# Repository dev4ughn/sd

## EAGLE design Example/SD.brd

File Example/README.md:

# SR Latch & Decade Counter Game

## Overview

Using an SR latch as the clock input for a decade counter to light up LEDs. The goal is to light up all the LEDs in the fastest time possible.

## Power Input

Two 3.0V coin cell lithium-ion batteries.

## SR Latch

Using two NOR gates on an IC. An LED will confirm the state of the SR latch.

## Decade Counter

Edge-triggered component that outputs high for a new pin every clock cycle.

## Firmware

This board does not have any programmable components so no firmware is required.

## Images

Schematic:

Board:

3D Render:

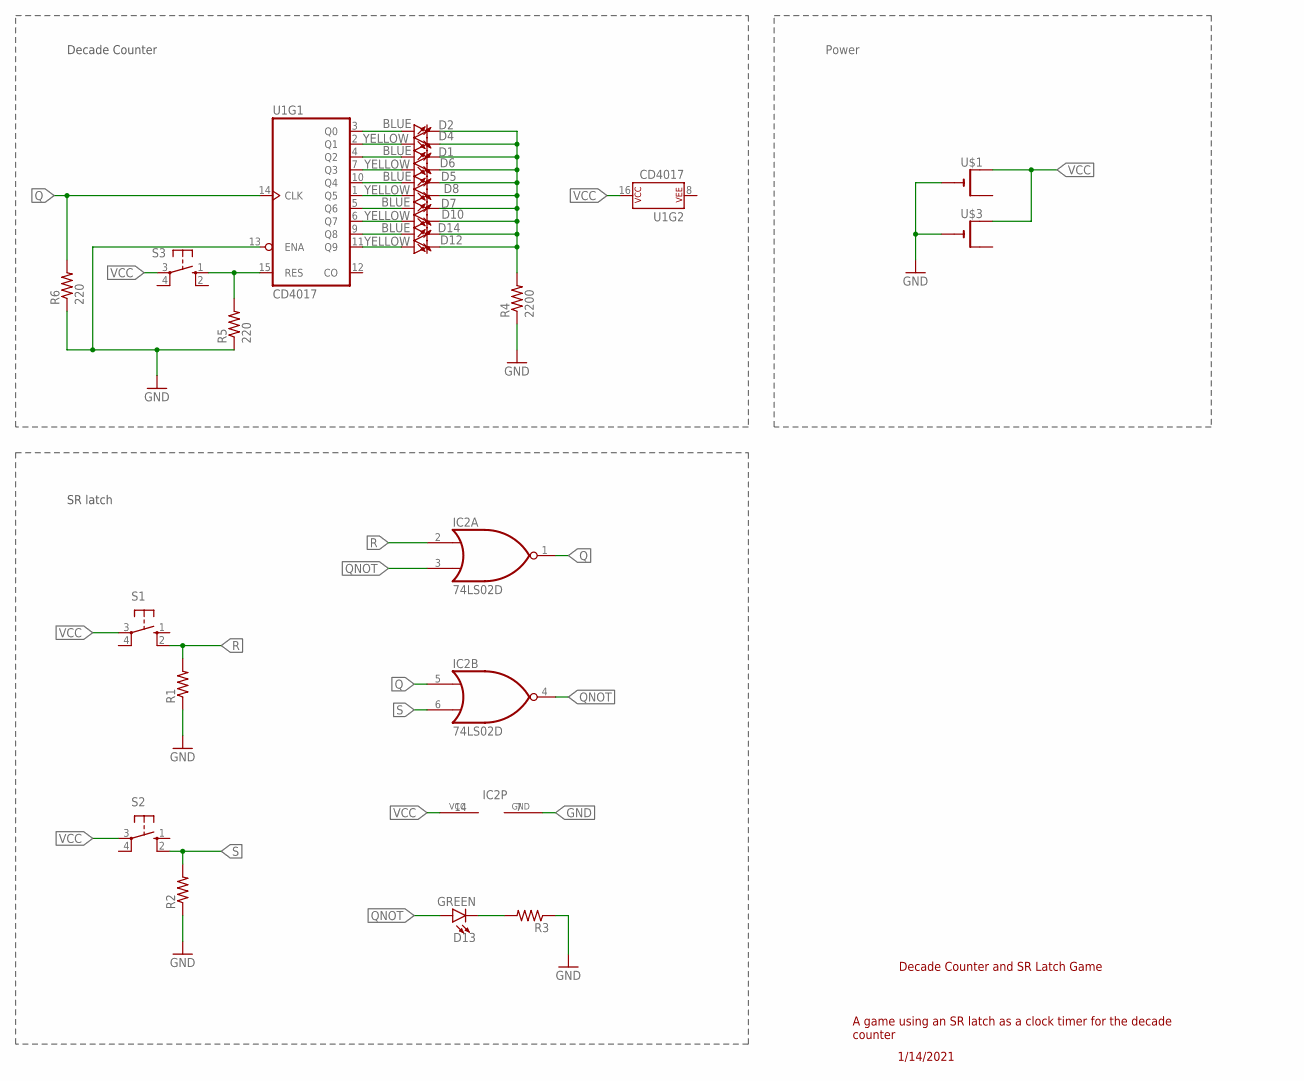
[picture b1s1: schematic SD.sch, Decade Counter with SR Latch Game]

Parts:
D1, D2, D5, D7, D14: BLUE; LED-0603
D4, D6, D8, D10, D12: YELLOW; LED0603
D13: GREEN; LED-0603
IC2: 74LS02D; SO14
R1, R2, R3: R-US_R0603; R0603
R4: 2200; R0603
R5, R6: 220; R0603
S1, S2, S3: 40-XX-ROUND; B3F-40XX-ROUND
U1: CD4017; DIP16
U$1, U$3: CR1220SMT; CR1220-SMD

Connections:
GND: IC2.7 (GND), R1.1, R2.1, R3.1, R4.1, R5.1, R6.1, U1.13 (ENA), U$1.-, U$3.-
unnamed: R5.2, S3.1 (S), U1.15 (RES)
unnamed: D13.C, R3.2
unnamed: D2.A, U1.3 (Q0)
unnamed: D4.A, U1.2 (Q1)
unnamed: D1.A, U1.4 (Q2)
unnamed: D6.A, U1.7 (Q3)
unnamed: D5.A, U1.10 (Q4)
unnamed: D8.A, U1.1 (Q5)
unnamed: D7.A, U1.5 (Q6)
unnamed: D10.A, U1.6 (Q7)
unnamed: D14.A, U1.9 (Q8)
unnamed: D12.A, U1.11 (Q9)
unnamed: D1.C, D2.C, D4.C, D5.C, D6.C, D7.C, D8.C, D10.C, D12.C, D14.C, R4.2
Q: IC2.1 (O), IC2.5 (I0), R6.2, U1.14 (CLK)
QNOT: IC2.3 (I1), IC2.4 (O)
R: IC2.2 (I0), R1.2, S1.2 (S1)
S: IC2.6 (I1), R2.2, S2.2 (S1)
VCC: IC2.14 (VCC), S1.3, S2.3, U1.16 (P$V+), U$1.+$1 (+), U$3.+$1 (+)

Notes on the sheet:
SR latch
Decade Counter
Power
Decade Counter and SR Latch Game
A game using an SR latch as a clock timer for the decade counter
1/14/2021

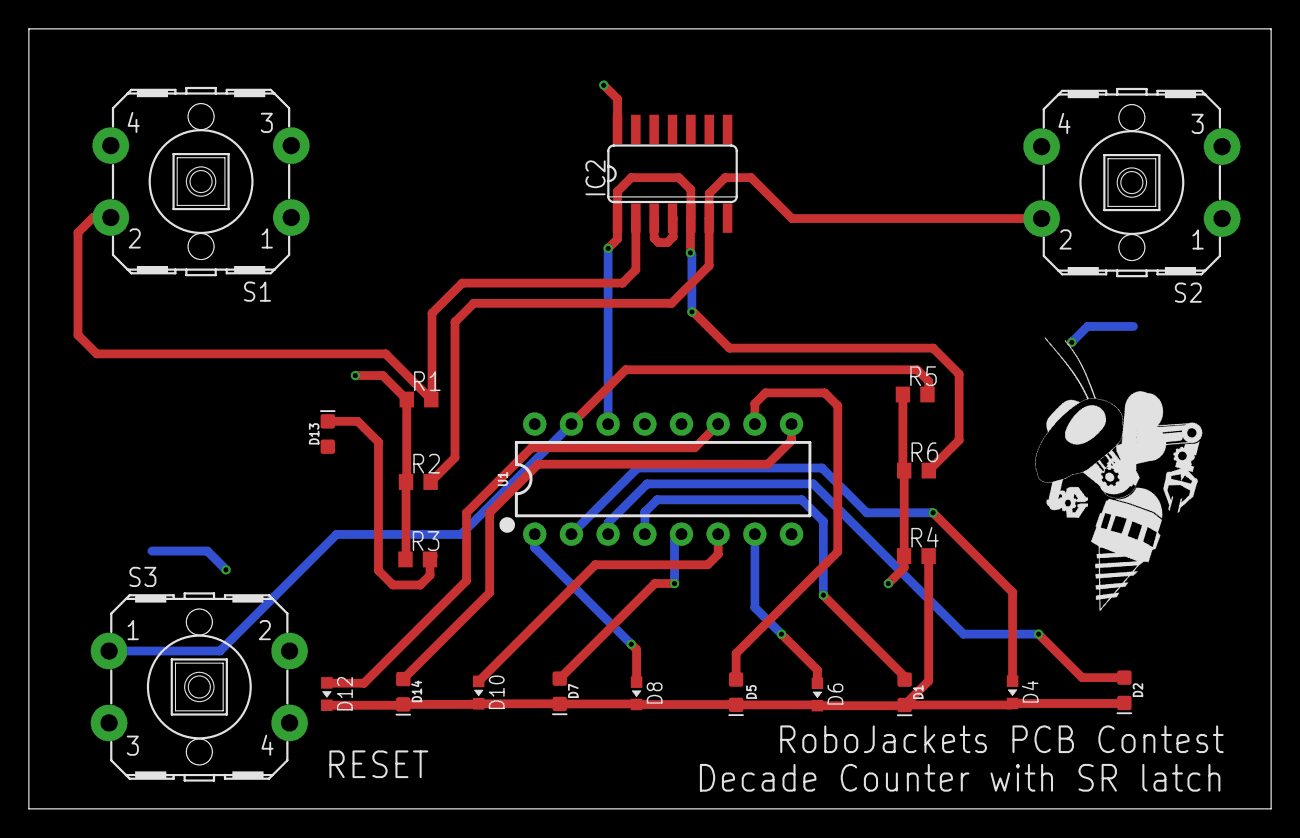
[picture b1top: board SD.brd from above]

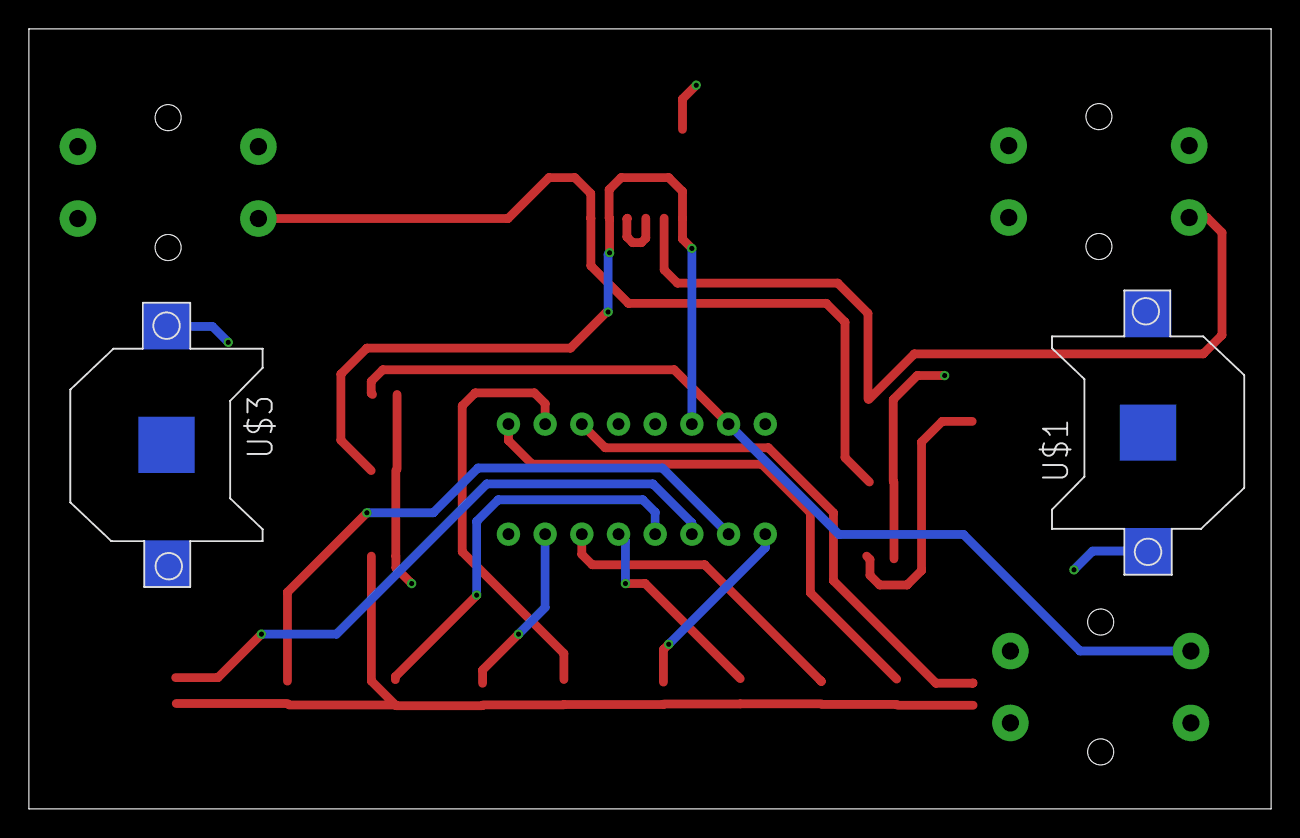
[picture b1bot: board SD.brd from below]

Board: 2 copper layers, 86.0 x 54.0 mm, 25 parts (2 on the bottom side), 19 nets.

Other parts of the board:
U$4: ROBOBUZZ_1.0X

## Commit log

2020-12-19 Delete motor
    commit test
2021-01-04 Update Example.sch
    Added labels to the schematic view of parts we need.
2021-01-08 added four new parts
    added button, cell, led, and nor gate
2021-01-09 add
    add parts
2021-01-09 Revert "add"
    This reverts commit c6e4ebc28e4f55c76fdda87922b953a09ff3b68b.
2021-01-09 sr latch
    finished sr latch
2021-01-10 Fixed issue of second NOR gate. However, did not delete second NOR gate.
    I could not change the attributes of the NOR gates.
2021-01-10 Added CD4017 Decade Counter
    Part can be found in the SparkFun-IC-Logiv Library
2021-01-12 decade counter
    leds for decade counter
2021-01-12 decade counter
    added clocks and EN
2021-01-12 Fixed multiple NOR gate issue
    Removed IC3A from the schematic
2021-01-12 placed items on board
    i placed everything on the board except for battery holders
2021-01-13 moved stuff
    move
2021-01-13 Revert "moved stuff"
    This reverts commit 32ee3d4f72a0406771ac1d0ac5515acdafe1b475.
2021-01-13 Added LEDs, made one Vcc, and updated board
2021-01-13 connected the reset button and change the titles for sheet
2021-01-13 change button and led position
2021-01-13 aligned LEDs
2021-01-13 moved parts
2021-01-14 made few routes except for gnd and vcc
2021-01-14 add vcc and gnd planes and finished routing
2021-01-14 Added a layer for Vcc and GND, removed some routes
    The GND routes and Vcc routes are connected to vias
2021-01-14 small changes
2021-01-14 add package
2021-01-14 created part for DC
2021-01-14 Update 3D Render on ReadMe
2021-01-14 images of board and schematic
2021-01-14 Updated Readme to include Board views and schem
2021-01-14 change file names
2021-01-14 changed folder name to 'contents'

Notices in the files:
parts and their libraries:
SparkFun-IC-Logic: Licensing: Creative Commons ShareAlike 4.0 International - https://creativecommons.org/licenses/by-sa/4.0
